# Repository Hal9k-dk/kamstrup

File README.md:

# kamstrup
Kamstrup IR-øje

Se http://wiki.hal9k.dk/projects/kamstrup for flere oplysninger.

DLMS kompatibel software:

https://github.com/bsdphk/PyKamstrup
https://github.com/Hal9k-dk/kamstrup/tree/master/Software%20eksempler/kamstrup_powermeter

IEC 62056 kompatibel software:

https://github.com/bsdphk/PyDLMS

Kamstrup MULTICAL kompatibel software:

https://github.com/Hal9k-dk/kamstrup/tree/master/Software%20eksempler/kamstrup_multical402
https://github.com/KenanV/KamstrupMultical66
https://github.com/golles/Home-Assistant-Sensor-MC66C
https://github.com/RuntimeError123/hass-mc66c

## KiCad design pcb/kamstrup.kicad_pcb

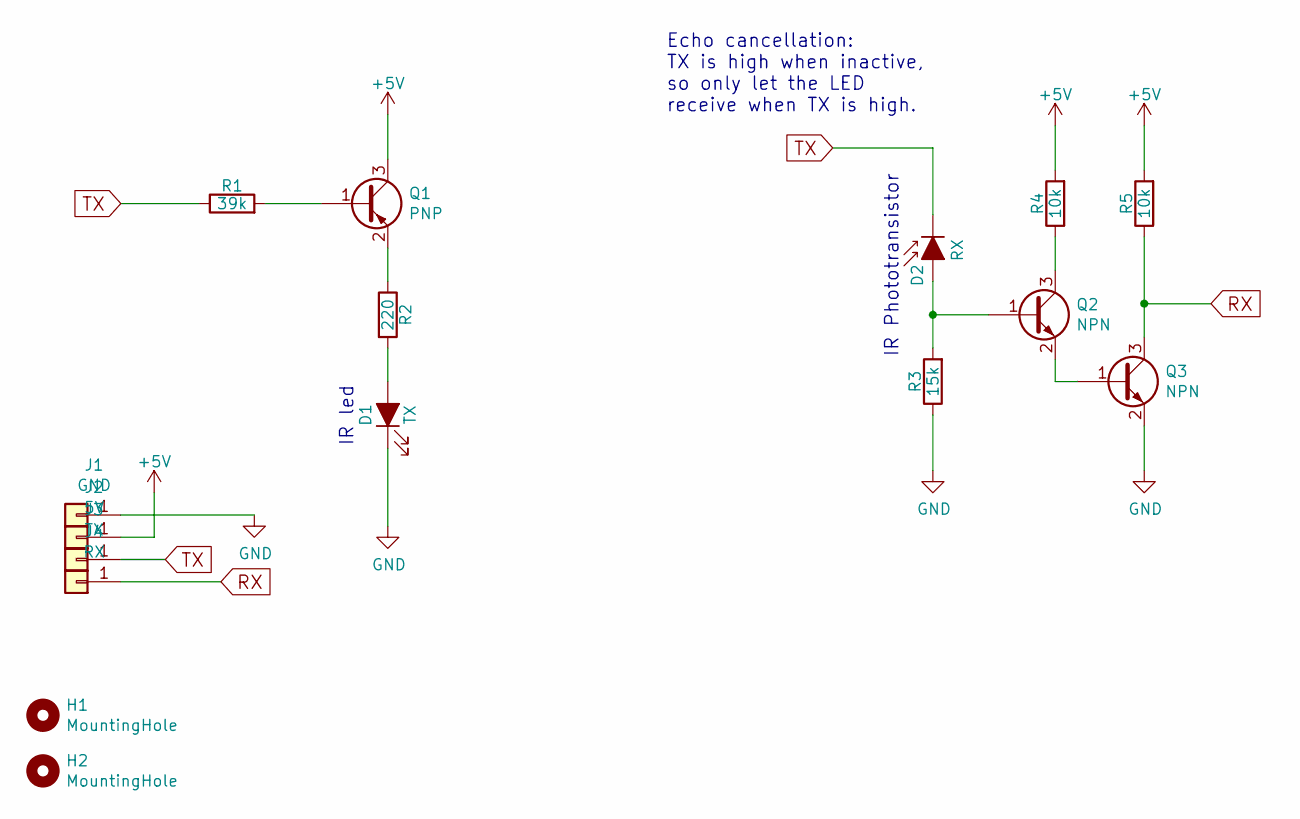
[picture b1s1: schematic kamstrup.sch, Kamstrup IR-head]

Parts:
D1: TX; LED_0603_1608Metric
D2: RX; LED_0603_1608Metric
H1, H2: MountingHole; MountingHole_2.2mm_M2
J1: GND; TestPoint_Pad_1.5x1.5mm
J2: 5V; TestPoint_Pad_1.5x1.5mm
J3: TX; TestPoint_Pad_1.5x1.5mm
J4: RX; TestPoint_Pad_1.5x1.5mm
Q1: PNP; SOT-23
Q2, Q3: NPN; SOT-23
R1: 39k; R_0603_1608Metric
R2: 220; R_0603_1608Metric
R3: 15k; R_0603_1608Metric
R4, R5: 10k; R_0603_1608Metric

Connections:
+5V: J2.1, Q1.3 (C), R4.2, R5.2
GND: D1.1 (K), J1.1, Q3.2 (E), R3.1
unnamed: D1.2 (A), R2.2
unnamed: D2.2 (A), Q2.1 (B), R3.2
unnamed: Q1.1 (B), R1.2
unnamed: Q1.2 (E), R2.1
unnamed: Q2.2 (E), Q3.1 (B)
unnamed: Q2.3 (C), R4.1
RX: J4.1, Q3.3 (C), R5.1
TX: D2.1 (K), J3.1, R1.1

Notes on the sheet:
Echo cancellation: TX is high when inactive, so only let the LED receive when TX is high.
IR Phototransistor
IR led

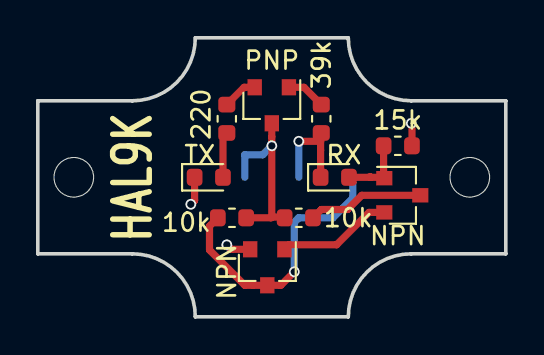
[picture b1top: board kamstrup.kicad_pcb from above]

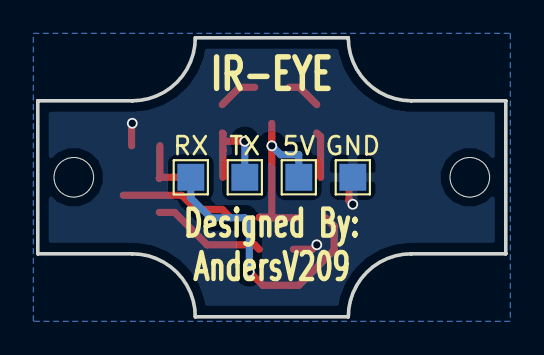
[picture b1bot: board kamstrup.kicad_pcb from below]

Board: 2 copper layers, 26.0 x 15.5 mm, 16 parts (4 on the bottom side), 10 nets.

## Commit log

2017-07-21 Initial commit.
2017-07-21 Add link to wiki.
2019-03-23 SMD version first commit
2019-03-23 Clean up and gerber files for pcb
2019-03-23 Readme update
2019-03-23 Added link to datasheet for components.
2020-05-28 tilføjelse af kode excempler
2021-11-16 Update README.md
    Update README.md
2022-01-17 Create kamstrup_influxdb.ino
    tilføjelse af et eksemel til at smide data i influxdb med en esp8266
2022-02-05 add multical402 to influxdb example
